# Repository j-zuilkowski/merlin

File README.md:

# Merlin

A personal, non-sandboxed agentic development assistant for macOS. Merlin connects to multiple LLM providers — remote and local — and gives an AI agent full access to your file system, shell, Xcode, GUI automation, and external services to work through development tasks autonomously. It includes a supervisor-worker multi-LLM routing layer and MLX LoRA self-training (MLX-format base models on Apple Silicon) to improve the execute slot on your own accepted sessions over time.

Built with Swift and SwiftUI for macOS 14+. Personal use only — not distributed; build from source via the steps in [`Requirements.md`](Requirements.md).

**Version 2.4.0** (build 26)

Current release gate: v2.4.0 is the full green E2E release gate. A release push requires the full GUI/test/provider/domain battery to pass, a release evidence report, and post-green screenshots. Electronics screenshots must be captured after the full battery is green by opening the generated KiCad files in KiCad, not from static generated images alone.

---

## What it does

## Screenshots

## Documentation

- [User Guide](Merlin/Docs/UserGuide.md) — using Merlin, providers, sessions, workflows, electronics tools, and project discipline.
- [Developer Manual](Merlin/Docs/DeveloperManual.md) — architecture, engine surfaces, tool registry, plugins, and developer workflows.
- [Release Notes v2.4.0](RELEASE-v2.4.0.md) — current release highlights, evidence gates, and screenshots.
- [Release Evidence Report](docs/e2e/2026-06-08-v2.4.0-release/REPORT.md) — gate-by-gate v2.4.0 validation artifacts.

## Capabilities

Merlin runs an agentic loop: you describe a task, the model calls tools (read files, run shell commands, build with Xcode, inspect UI, write code), reads the results, and continues until the task is complete. You review staged changes before they land on disk.

**Multi-project workspace** — a single window holds multiple open projects simultaneously. Each project has its own session list in the sidebar; the content area shows whichever session is active. Workspace state (open projects, active session) persists across relaunches.

**Session history** — every session is saved to disk after each turn, scoped per project. Prior sessions appear in the sidebar with relative timestamps. Sessions can be archived (hidden) or recalled to active status. Session titles are auto-generated from the first user message, matching Claude app and Codex behaviour.

**Multi-LLM Supervisor-Worker** — tasks are classified by complexity and routed to the right LLM slot (execute, reason, orchestrate, vision). A critic layer scores outputs; a planner layer decomposes high-stakes work. Model performance is tracked per-model per-task type and stored for training.

**Electronics / KiCad Domain** — a full electronics workflow built on the bus-backed `plugins/electronics` runtime plugin: raster/PDF schematic ingestion, design-intent approval, Circuit IR generation, concrete component evidence, KiCad project and footprint generation, FreeRouting-backed autoroute, ERC/DRC/SPICE/fab verification gates, vendor-native BOM and order workflows. Evidence-gated completion and high-stakes signoff boundaries block irreversible manufacturing actions without explicit approval.

**Multi-Domain Sessions** — each session carries its own active domain IDs. Switching from a software session to an electronics session is instant; the engine, critic, and task-type routing all follow without touching other open sessions.

**Local Memory Backend** — session memories are stored in an on-device SQLite vector store (`LocalVectorPlugin`, `NLContextualEmbedding`, 512-dim) scoped per project path. xcalibre-server is retained for book-content RAG only.

**Behavioral Reliability** — a circuit breaker halts or warns after consecutive critic failures; a grounding confidence signal (`GroundingReport`) surfaces RAG chunk count, average cosine score, and staleness on every turn so you can see when the model is reasoning over thin or stale retrieval.

**Budget-Aware Execution** (v2.1) — every LLM request is sized to the active provider's context window before it is sent. A pre-flight estimator gates each call; working-set caps bound the system prompt, RAG injection, recent turns, and tool-call bursts independently. Oversized work is decomposed into smaller substeps first, with cross-provider routing to a larger-context model only as a last resort.

**LoRA Self-Training** — on an M4 Mac with 128GB unified memory, Merlin can fine-tune a local **MLX-format** model (via MLX-LM) on your own accepted sessions. Automatic training requires an MLX base; GGUF and HF-safetensors bases cannot be trained by `mlx_lm.lora`. The trained adapter is served by any MLX-native runtime — `mlx_lm.server` (the default), LM Studio, or vLLM-Metal after a one-shot `mlx_lm.fuse` for text-only experiments, though vLLM-Metal is non-working for the current Merlin general+vision pair workflow and should be avoided for the foreseeable future. For GGUF providers (Ollama / Jan.ai / LocalAI / llama.cpp), an additional GGUF-conversion step deploys the fine-tuned model; Mistral.rs cannot serve MoE models on Metal regardless.

**Project Discipline** (v2.2) — Merlin can enforce construction discipline on any project: TDD task pairs, comprehensive user-manual coverage, WHY-comments where warranted, prose readability, and task-file/code sync. Five `/project:*` skills (`init`, `task`, `revise`, `release`, `adopt`) handle creation; a `DisciplineEngine` plus git hooks enforce the rules automatically. `/project:adopt` applies the discipline to an existing codebase.

**Full Green E2E Release Gate** (v2.4) — release readiness is a blocking evidence surface. The current release path requires core tests, GUI bootstrapping, focused visual tests, live-provider coverage, local-provider pair smokes, xcalibre RAG verification, S1/S2 capability convergence, electronics/KiCad verification, service cleanup, and a passing evidence report before tagging or publishing.

See [`FEATURES.md`](FEATURES.md) for a complete capability reference.  
See [`spec.md`](spec.md) for implementation details and design decisions.

---

## Providers

Remote: **Anthropic**, **DeepSeek**, **OpenAI**, **Qwen**, **OpenRouter**

Local provider status (validated live on May 27, 2026):

Preferred local provider: **llama.cpp router mode**. Use it first for local
general+vision work because one router-mode `llama-server` can own the GGUF text
model, the GGUF vision model, and the vision `mmproj` behind one OpenAI-compatible
endpoint. LM Studio and Jan.ai remain reliable alternatives.

| Provider | Status | Notes |
|---|---|---|
| llama.cpp (router mode) | Preferred reliable | First-class provider at `http://localhost:8081/v1`; one router-mode server handled the local general+vision GGUF pair |
| LM Studio | Reliable alternative | General + vision pair passed live calibration |
| Jan.ai | Reliable alternative | General + vision pair passed live calibration |
| LocalAI | Non-working for Merlin full surface | Text, streaming, and vision responded, but tool-call requests returned plain content without OpenAI `tool_calls` |
| Ollama | Non-working for Merlin full surface | Text works, but the tested Qwen3-VL path crashes the runner on real image requests; skip until upstream fixes land |
| vLLM-Metal | Non-working / avoid | Text and auto tool calls can work, but forced tool choice is unreliable and vision is not implemented on Metal; avoid for the foreseeable future |
| Mistral.rs | Non-working for tested model | The tested Qwen3 MoE GGUF model loads, then fails on first inference on Apple Metal |

Upstream blocker tracking for the malfunctioning local providers lives in
[`docs/local-provider-configs/RESULTS.md`](docs/local-provider-configs/RESULTS.md).

`/calibrate` is live-validated in the app against the supported local providers. The GUI flow now completes picker → running → report, surfaces scorer failures materially better than before, and reports degraded critic fallback explicitly when it occurs.

Routing is driven by explicit slot assignments (Execute, Reason, Orchestrate, Vision) in
Settings → Role Slots. The sidebar slot-status panel reflects those assignments directly;
enabled provider inventory alone does not configure routing. API keys are stored in
`~/.merlin/api-keys.json` during Debug/dev-loop builds and in macOS Keychain for
Release builds. The release/pre-push path and CI block tracked local-only key
files such as `api-keys.json`, `.env*`, and `secrets.json`.

---

## Requirements

- macOS 14 (Sonoma) or later
- Xcode 15.4 or later
- [XcodeGen](https://github.com/yonaskolb/XcodeGen) (`brew install xcodegen`)

---

## Build & Run

```bash
# Generate the Xcode project
xcodegen generate

# Build and launch (Debug)
xcodebuild -scheme Merlin -configuration Debug \
    SYMROOT="$(pwd)/build" \
    CODE_SIGNING_ALLOWED=NO 2>&1 | grep -E 'error:|BUILD SUCCEEDED|BUILD FAILED'

open build/Debug/Merlin.app
```

Or open `Merlin.xcodeproj` in Xcode and run from there.

---

## Project layout

```
Merlin/             Main application target (Swift sources)
MerlinTests/        Unit and integration tests
MerlinLiveTests/    Real-provider API tests (run manually)
MerlinE2ETests/     Full agentic loop + UI tests (run manually)
TestHelpers/        Shared test utilities (MockProvider, EngineFactory, …)
TestTargetApp/      Fixture app for GUI automation tests
tasks/             Task-by-task implementation sheets
scripts/            DMG packaging script
```

---

## Configuration

| File | Purpose |
|---|---|
| `~/.merlin/config.toml` | Hooks, memories, reasoning overrides, toolbar actions |
| `~/.merlin/mcp.json` | MCP server definitions |
| `~/.merlin/skills/` | Personal slash-command skills |
| `~/.merlin/agents/` | Custom subagent definitions |
| `~/.merlin/memories/` | Accepted AI-generated memories |
| `~/.merlin/workspace.json` | Open projects and active session (persisted across relaunches) |
| `~/.merlin/layout-workspace.json` | Pane layout (sidebar width, visible panes) |
| `~/Library/Application Support/Merlin/providers.json` | Provider configuration |
| `~/Library/Application Support/Merlin/auth.json` | Auth gate allow/deny patterns |
| `~/Library/Application Support/Merlin/sessions/<project-id>/` | Per-project session history |

---

## Running tests

```bash
# Unit + integration (fast, no network)
xcodebuild -scheme MerlinTests test \
    -destination 'platform=macOS' \
    -derivedDataPath /tmp/merlin-derived 2>&1 \
    | grep -E 'Test.*passed|Test.*failed|BUILD SUCCEEDED|BUILD FAILED'

# Live provider tests (requires API keys)
RUN_LIVE_TESTS=1 xcodebuild -scheme MerlinTests-Live test \
    -destination 'platform=macOS' \
    -derivedDataPath /tmp/merlin-derived
```

---

## Release Readiness

Merlin v2.4.0 is not considered release-push-ready from version metadata alone. The release push requires the full green E2E battery described in [`spec.md`](spec.md): full `MerlinTests`, full `MerlinUITests`, focused visual tests, allowed live-provider skips only for missing keys, local-provider pair smokes with clean shutdown, xcalibre RAG verification, S1/S2 convergence, and electronics/KiCad verification.

After the full battery is green, open the generated KiCad schematic and open the generated KiCad PCB in KiCad, then capture release screenshots of the schematic editor, PCB editor, routed board/layer views, and 3D board view when available. GitHub feature screenshots are captured at the same post-green stage.

Screenshot destinations:

- GitHub Release assets: upload release-marketing screenshots and KiCad screenshots to the `v2.4.0` GitHub Release as release assets.
- README-linked screenshots: commit durable public images under `docs/assets/screenshots/v2.4.0/`.
- Evidence-only screenshots: retain validation-only images under `docs/e2e/<date>-v2.4.0-release/screenshots/` with the E2E report.

---

## Packaging

```bash
bash scripts/package-dmg.sh <version>
# → dist/Merlin-<version>.dmg
```

Or build a release DMG directly:

```bash
xcodebuild -scheme Merlin -configuration Release \
    -derivedDataPath /tmp/merlin-release \
    -destination 'platform=macOS' build

hdiutil create -volname "Merlin <version>" \
    -srcfolder /tmp/merlin-release/Build/Products/Release/Merlin.app \
    -ov -format UDZO dist/Merlin-$(date +%Y-%m-%d)-v<version>.dmg
```

Requires [`create-dmg`](https://github.com/create-dmg/create-dmg) (`brew install create-dmg`) or falls back to `hdiutil`.

---

## Further reading

- [`FEATURES.md`](FEATURES.md) — complete feature reference
- [`spec.md`](spec.md) — system design and implementation decisions
- [`llm.md`](llm.md) — LLM provider and context design details
- [`skill-standard.md`](skill-standard.md) — skill and plugin authoring guide
- [User Guide](Merlin/Docs/UserGuide.md) — in-app user guide (Help menu)
- [Developer Manual](Merlin/Docs/DeveloperManual.md) — in-app developer reference (Help menu)
- [Release Notes v2.4.0](RELEASE-v2.4.0.md) — current release notes

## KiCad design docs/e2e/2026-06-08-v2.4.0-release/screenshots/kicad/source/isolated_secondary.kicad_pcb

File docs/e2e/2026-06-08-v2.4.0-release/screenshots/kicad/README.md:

# KiCad Screenshot Evidence - Task 512

This bundle supersedes the Task 511 KiCad screenshots. Task 512 regenerated the
source artifacts from the final green AmpDemo PCB slice, reopened those copied
files in KiCad 10.0.3, and captured fresh editor screenshots after user review
found the prior evidence unusable.

## Source

- `source/isolated_secondary.kicad_pro`
- `source/isolated_secondary.kicad_sch`
- `source/isolated_secondary.kicad_pcb`
- `source/8FDFC0B1-C9C8-4CED-9E02-9374462932BA-component_matrix.json`
- `source/94B2FA49-5634-45BD-AB71-95C35C9E8A75-footprint_assignment.json`
- `source/drc.json`
- `source/drc-rerun.json`

## Screenshots And Exports

- `schematic-editor-screenshot.png` - copied schematic opened in KiCad
  Schematic Editor; visible connectors include `JSEC`, `JIN`, and `JSPK`.
- `pcb-editor-screenshot.png` - copied board opened in KiCad PCB Editor with
  visible routed copper; the KiCad status bar shows 62 pads, 36 vias, 72 track
  segments, 18 nets, and 0 unrouted items.
- `board-3d-viewer-screenshot.png` - copied board opened in KiCad GUI 3D
  Viewer.
- `schematic.pdf` - KiCad CLI schematic PDF export.
- `schematic-svg/isolated_secondary.svg` and
  `schematic-svg/isolated_secondary.png` - KiCad CLI schematic export and PNG
  preview.
- `layers/front-copper.svg` and `layers/front-copper.png` - front copper/layer
  export.
- `layers/back-copper.svg` and `layers/back-copper.png` - back copper/layer
  export.
- `layers/routed-composite.svg` and `layers/routed-composite.png` - combined
  routed/layer export.
- `board-3d-render.png` - deterministic KiCad CLI 3D render.

## Verification

`source/drc.json` is the runtime DRC report from the final green generated
board. It records:

- 0 DRC violations
- 0 unconnected items
- 0 schematic parity issues
- KiCad 10.0.3

`source/drc-rerun.json` is the copied-project KiCad CLI rerun. It records 0 DRC
violations and 0 unconnected items, with 59 schematic parity warnings. That
copied-bundle parity limitation is preserved as evidence and this screenshot
bundle is not a `FAB_READY` claim.

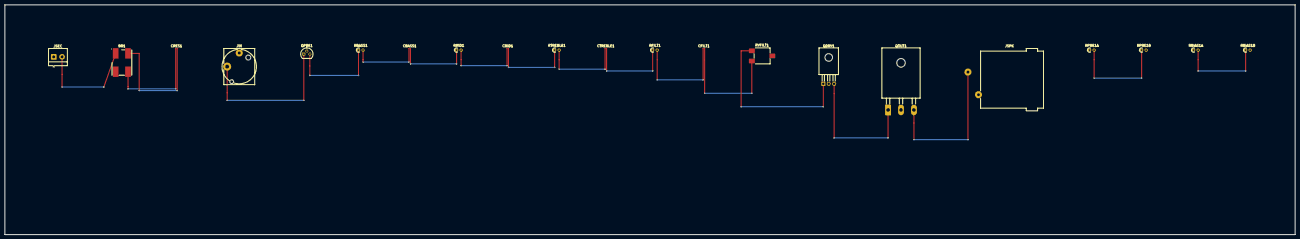
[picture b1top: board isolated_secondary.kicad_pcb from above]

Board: 2 copper layers, 543.6 x 96.8 mm, 21 parts (0 on the bottom side), 18 nets.

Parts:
BR1: BR1-MPN; Diode_Bridge_Bourns_CD-DF4xxS
CBASS1: 100nF; C_0201_0603Metric
CFILT1: 47nF; C_0201_0603Metric
CMID1: 22nF; C_0201_0603Metric
CRES1: 10000uF; C_0201_0603Metric
CTREBLE1: 470pF; C_0201_0603Metric
JIN: JIN-MPN; Jack_6.35mm_Neutrik_NJ2FD-V_Vertical
JSEC: JSEC-MPN; TerminalBlock_4Ucon_1x02_P3.50mm_Horizontal
JSPK: JSPK-MPN; Jack_speakON_Neutrik_NL2MDXX-H-3_Horizontal
QDRV1: QDRV1-MPN; TO-126-3_Horizontal_TabDown
QOUT1: QOUT1-MPN; TO-247-3_Horizontal_TabDown
QPRE1: QPRE1-MPN; TO-92
RBASS1: 1MOhm; R_Axial_DIN0204_L3.6mm_D1.6mm_P1.90mm_Vertical
RBIAS1A: 10kOhm; R_Axial_DIN0204_L3.6mm_D1.6mm_P1.90mm_Vertical
RBIAS1B: 1kOhm; R_Axial_DIN0204_L3.6mm_D1.6mm_P1.90mm_Vertical
RFILT1: 10kOhm; R_Axial_DIN0204_L3.6mm_D1.6mm_P1.90mm_Vertical
RMID1: 25kOhm; R_Axial_DIN0204_L3.6mm_D1.6mm_P1.90mm_Vertical
RPRE1A: 1MOhm; R_Axial_DIN0204_L3.6mm_D1.6mm_P1.90mm_Vertical
RPRE1B: 100kOhm; R_Axial_DIN0204_L3.6mm_D1.6mm_P1.90mm_Vertical
RTREBLE1: 250kOhm; R_Axial_DIN0204_L3.6mm_D1.6mm_P1.90mm_Vertical
RVFILT1: 100kOhm; Potentiometer_ACP_CA6-VSMD_Vertical

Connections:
AC_SEC1: BR1.1, JSEC.2
DRV_OUT: QDRV1.3, QOUT1.1
FILTER1_INTERNAL_CFILT1_RVFILT1: CFILT1.2, RVFILT1.1
FILTER1_INTERNAL_RFILT1_CFILT1: CFILT1.1, RFILT1.2
FILTER_OUT: QDRV1.1, RVFILT1.3
GND: BR1.4, CRES1.2
GUITAR_IN: JIN.S, QPRE1.1
PRE_OUT: QPRE1.3, RBASS1.1
RBIAS1_INTERNAL_RBIAS1A_RBIAS1B: RBIAS1A.2, RBIAS1B.1
RPRE1_INTERNAL_RPRE1A_RPRE1B: RPRE1A.2, RPRE1B.1
SPK_OUT: JSPK.1+, QOUT1.3
TONE1_INTERNAL_CBASS1_RMID1: CBASS1.2, RMID1.1
TONE1_INTERNAL_CMID1_RTREBLE1: CMID1.2, RTREBLE1.1
TONE1_INTERNAL_RBASS1_CBASS1: CBASS1.1, RBASS1.2
TONE1_INTERNAL_RMID1_CMID1: CMID1.1, RMID1.2
TONE1_INTERNAL_RTREBLE1_CTREBLE1: CTREBLE1.1, RTREBLE1.2
TONE_OUT: CTREBLE1.2, RFILT1.1
VRAW: BR1.3, CRES1.1

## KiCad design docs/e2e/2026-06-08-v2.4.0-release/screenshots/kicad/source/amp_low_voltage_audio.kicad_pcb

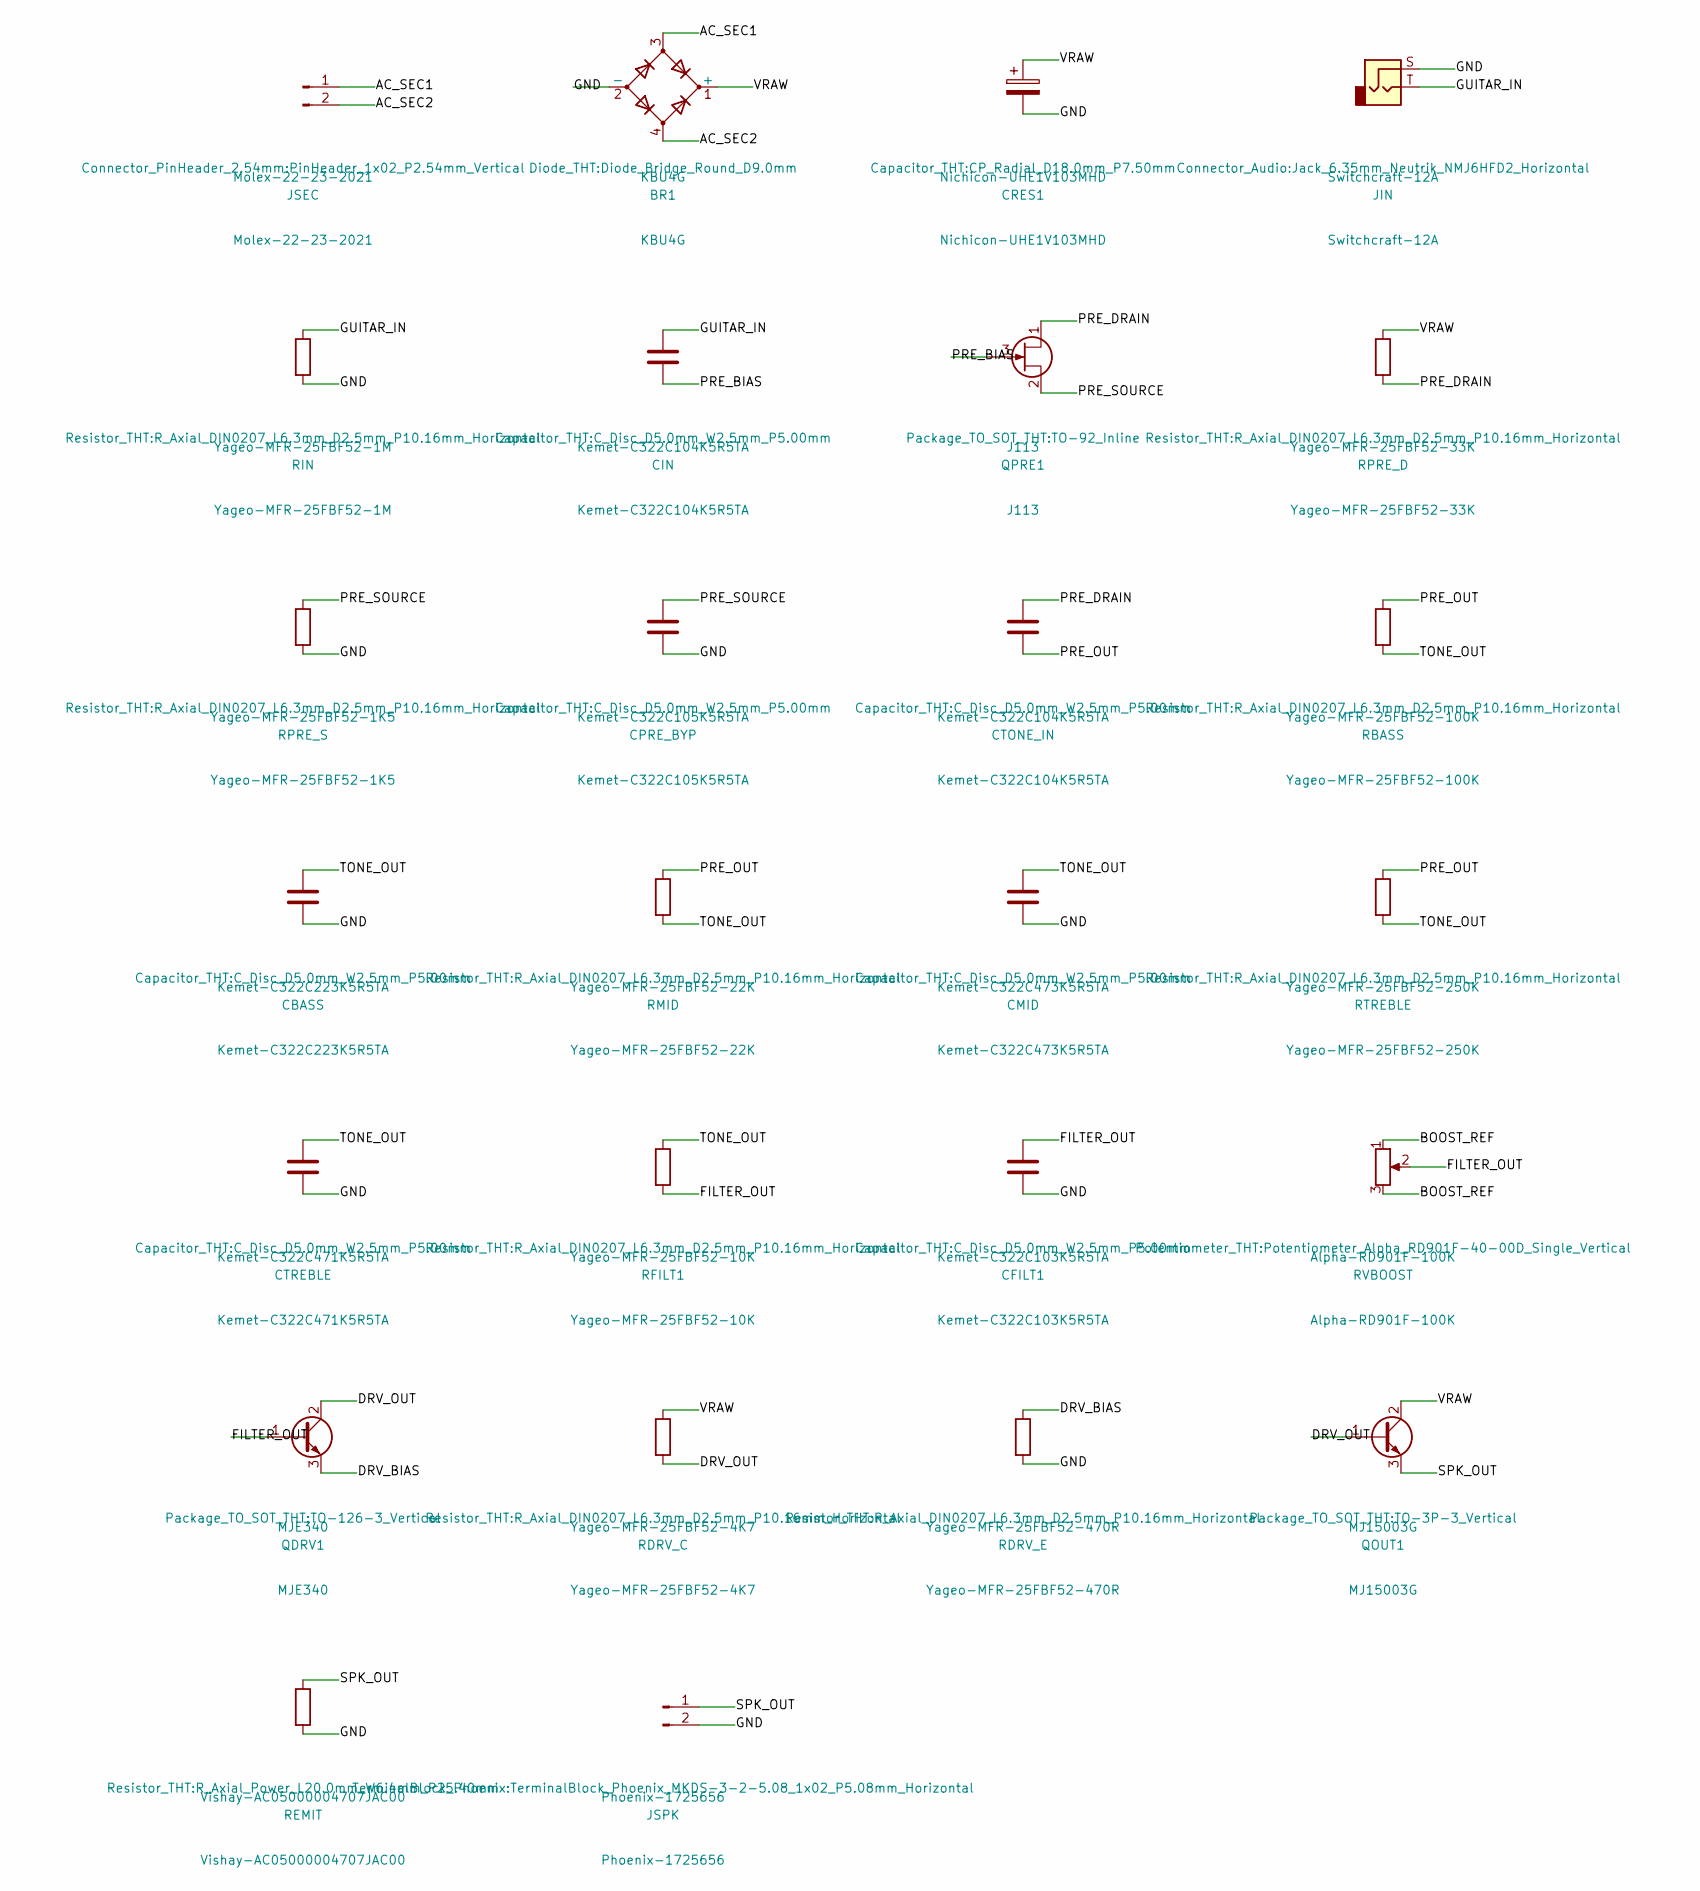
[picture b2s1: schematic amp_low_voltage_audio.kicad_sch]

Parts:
BR1: KBU4G; Diode_Bridge_Round_D9.0mm; ManufacturerPartNumber KBU4G
CBASS: Kemet-C322C223K5R5TA; C_Disc_D5.0mm_W2.5mm_P5.00mm; ManufacturerPartNumber Kemet-C322C223K5R5TA
CFILT1: Kemet-C322C103K5R5TA; C_Disc_D5.0mm_W2.5mm_P5.00mm; ManufacturerPartNumber Kemet-C322C103K5R5TA
CIN: Kemet-C322C104K5R5TA; C_Disc_D5.0mm_W2.5mm_P5.00mm; ManufacturerPartNumber Kemet-C322C104K5R5TA
CMID: Kemet-C322C473K5R5TA; C_Disc_D5.0mm_W2.5mm_P5.00mm; ManufacturerPartNumber Kemet-C322C473K5R5TA
CPRE_BYP: Kemet-C322C105K5R5TA; C_Disc_D5.0mm_W2.5mm_P5.00mm; ManufacturerPartNumber Kemet-C322C105K5R5TA
CRES1: Nichicon-UHE1V103MHD; CP_Radial_D18.0mm_P7.50mm; ManufacturerPartNumber Nichicon-UHE1V103MHD
CTONE_IN: Kemet-C322C104K5R5TA; C_Disc_D5.0mm_W2.5mm_P5.00mm; ManufacturerPartNumber Kemet-C322C104K5R5TA
CTREBLE: Kemet-C322C471K5R5TA; C_Disc_D5.0mm_W2.5mm_P5.00mm; ManufacturerPartNumber Kemet-C322C471K5R5TA
JIN: Switchcraft-12A; Jack_6.35mm_Neutrik_NMJ6HFD2_Horizontal; ManufacturerPartNumber Switchcraft-12A
JSEC: Molex-22-23-2021; PinHeader_1x02_P2.54mm_Vertical; ManufacturerPartNumber Molex-22-23-2021
JSPK: Phoenix-1725656; TerminalBlock_Phoenix_MKDS-3-2-5.08_1x02_P5.08mm_Horizontal; ManufacturerPartNumber Phoenix-1725656
QDRV1: MJE340; TO-126-3_Vertical; ManufacturerPartNumber MJE340
QOUT1: MJ15003G; TO-3P-3_Vertical; ManufacturerPartNumber MJ15003G
QPRE1: J113; TO-92_Inline; ManufacturerPartNumber J113
RBASS: Yageo-MFR-25FBF52-100K; R_Axial_DIN0207_L6.3mm_D2.5mm_P10.16mm_Horizontal; ManufacturerPartNumber Yageo-MFR-25FBF52-100K
RDRV_C: Yageo-MFR-25FBF52-4K7; R_Axial_DIN0207_L6.3mm_D2.5mm_P10.16mm_Horizontal; ManufacturerPartNumber Yageo-MFR-25FBF52-4K7
RDRV_E: Yageo-MFR-25FBF52-470R; R_Axial_DIN0207_L6.3mm_D2.5mm_P10.16mm_Horizontal; ManufacturerPartNumber Yageo-MFR-25FBF52-470R
REMIT: Vishay-AC05000004707JAC00; R_Axial_Power_L20.0mm_W6.4mm_P25.40mm; ManufacturerPartNumber Vishay-AC05000004707JAC00
RFILT1: Yageo-MFR-25FBF52-10K; R_Axial_DIN0207_L6.3mm_D2.5mm_P10.16mm_Horizontal; ManufacturerPartNumber Yageo-MFR-25FBF52-10K
RIN: Yageo-MFR-25FBF52-1M; R_Axial_DIN0207_L6.3mm_D2.5mm_P10.16mm_Horizontal; ManufacturerPartNumber Yageo-MFR-25FBF52-1M
RMID: Yageo-MFR-25FBF52-22K; R_Axial_DIN0207_L6.3mm_D2.5mm_P10.16mm_Horizontal; ManufacturerPartNumber Yageo-MFR-25FBF52-22K
RPRE_D: Yageo-MFR-25FBF52-33K; R_Axial_DIN0207_L6.3mm_D2.5mm_P10.16mm_Horizontal; ManufacturerPartNumber Yageo-MFR-25FBF52-33K
RPRE_S: Yageo-MFR-25FBF52-1K5; R_Axial_DIN0207_L6.3mm_D2.5mm_P10.16mm_Horizontal; ManufacturerPartNumber Yageo-MFR-25FBF52-1K5
RTREBLE: Yageo-MFR-25FBF52-250K; R_Axial_DIN0207_L6.3mm_D2.5mm_P10.16mm_Horizontal; ManufacturerPartNumber Yageo-MFR-25FBF52-250K
RVBOOST: Alpha-RD901F-100K; Potentiometer_Alpha_RD901F-40-00D_Single_Vertical; ManufacturerPartNumber Alpha-RD901F-100K

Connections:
AC_SEC1: BR1.3, JSEC.1
AC_SEC2: BR1.4, JSEC.2
BOOST_REF: RVBOOST.1, RVBOOST.3
DRV_BIAS: QDRV1.3 (E), RDRV_E.1
DRV_OUT: QDRV1.2 (C), QOUT1.1 (B), RDRV_C.2
FILTER_OUT: CFILT1.1, QDRV1.1 (B), RFILT1.2, RVBOOST.2
GND: BR1.2 (-), CBASS.2, CFILT1.2, CMID.2, CPRE_BYP.2, CRES1.2, CTREBLE.2, JIN.S, JSPK.2, RDRV_E.2, REMIT.2, RIN.2, RPRE_S.2
GUITAR_IN: CIN.1, JIN.T, RIN.1
PRE_BIAS: CIN.2, QPRE1.3 (G)
PRE_DRAIN: CTONE_IN.1, QPRE1.1 (D), RPRE_D.2
PRE_OUT: CTONE_IN.2, RBASS.1, RMID.1, RTREBLE.1
PRE_SOURCE: CPRE_BYP.1, QPRE1.2 (S), RPRE_S.1
SPK_OUT: JSPK.1, QOUT1.3 (E), REMIT.1
TONE_OUT: CBASS.1, CMID.1, CTREBLE.1, RBASS.2, RFILT1.1, RMID.2, RTREBLE.2
VRAW: BR1.1 (+), CRES1.1, QOUT1.2 (C), RDRV_C.1, RPRE_D.1

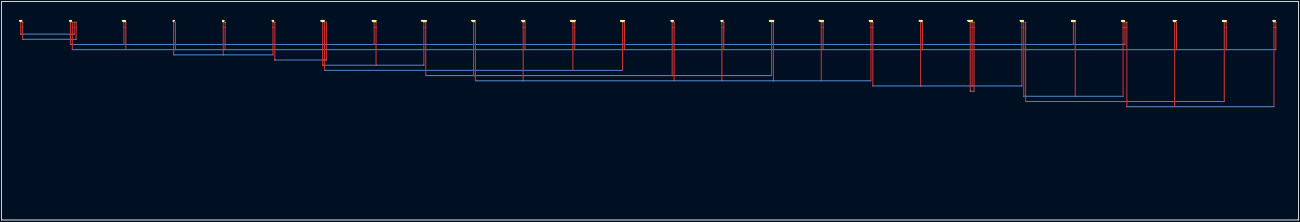
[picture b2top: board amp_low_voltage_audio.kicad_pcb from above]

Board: 2 copper layers, 1751.3 x 295.0 mm, 26 parts (0 on the bottom side), 15 nets.

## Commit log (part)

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2026-05-16 Phase 294a — RAG sources HTML tests (failing)
2026-05-16 Phase 294b — RAG sources HTML
2026-05-16 Phase 295a — Subagent block HTML tests (failing)
2026-05-16 Phase 296a — Subagent sidebar tests (failing)
2026-05-16 Phase 296b — Subagent sidebar
2026-05-16 Phase 297b — merlin-discipline CLI
2026-05-16 Phase 298a — Discipline event stream tests (failing)
2026-05-16 Phase 298b — Discipline event stream
2026-05-16 Phase 299b — Git hook wiring
2026-05-16 Phase 300a — Discipline generator tools tests (failing)
2026-05-16 Phase 301 — Remove unused versionBumpCandidate finding category
2026-05-16 Phase 302a — Info.plist permission strings tests (failing)
2026-05-16 Phase 302c — Revive the MerlinTests-Live scheme (post-145b rot)
2026-05-16 Phase 303a — Eval harness tests (failing)
2026-05-16 Phase 303b — Eval harness
2026-05-16 Phase 304b — Discipline chip shows true finding count
2026-05-16 Phase 305 — Wire the dead View-menu commands
2026-05-16 Phase 306b — Accessibility-identifier pass across the UI surface
2026-05-16 Relocate SURFACE-INVENTORY.md into phases/; track Liveness Discipline batch
2026-05-16 Phase 307b — TargetGateScanner: flag targets the build gate never compiles
2026-05-16 Phase 308a — StubMarkerScanner tests (failing)
2026-05-16 Phase 308b — StubMarkerScanner: surface unfinished code as discipline findings
2026-05-16 Phase 309b — ReachabilityScanner: flag unwired views and uninjected env objects
2026-05-16 Phase 310a — DocReferenceGraph fenced-block tests (failing)
2026-05-16 Phase 311a — LivenessGate tests (failing)
2026-05-16 Phase 311b — LivenessGate: pre-commit hook blocks ungated targets
2026-05-16 Phase 313a — Discipline gate auto-install tests (failing)
2026-05-16 Phase 313b — Auto-arm the discipline pre-commit gate at app launch
2026-05-16 Phase 314a — TargetGateScanner dependency-following tests (failing)
2026-05-16 Phase 315a — merlin-discipline scan command tests (failing)
2026-05-16 Phase 315b — merlin-discipline scan: print all discipline findings
2026-05-16 Phase 316b — DocReferenceGraph skips phases/ and knows test symbols
2026-05-16 Phase 317a — ReachabilityScanner injection-detection tests (failing)
2026-05-16 Phase 318a — StubMarkerScanner tuning tests (failing)
2026-05-16 Phase 318b — StubMarkerScanner skips .cancel buttons and multi-line strings
2026-05-17 Phase 319a — DocReferenceGraph precision tests (failing)
2026-05-17 Phase 320a — WorkerDiffViewActionTests (failing)
2026-05-17 Phase 320b — Wire WorkerDiffView reject-all / accept-and-merge
2026-05-17 Phase 321b — DocReferenceGraph extractEnumCaseNames strips // comments
2026-05-17 Phase 322 — Remove dead TelemetryEmitter setters
2026-05-17 Phase 323a — PhaseScanner doc-coverage & drift-severity tests (failing)
2026-05-17 Phase 324a — PhaseScanner symbol-matching tests (failing)
2026-05-17 Phase 324b — PhaseScanner symbol-matching accuracy
2026-05-17 Phase 325b — AccessibilityID gap-fill: the 12 controls phase 306 missed
2026-05-17 Phase 326 — Eval capability harness (S1–S6), self-launching services
2026-05-17 Phase 328 — Eval surface harness (S7–S11)
2026-05-17 Phase 329 — Eval render harness (S10 chat rendering)
2026-05-17 Phase 330 — Eval operator harness (S12–S17)
2026-05-17 Phase 331b — DisciplineExclusions blacklist
2026-05-17 Phase 332 — Relocate merlin-eval into the merlin repo
2026-05-17 Sync architecture.md discipline enums with implemented code
2026-05-17 Fix MerlinTests-Live scheme: RUN_LIVE_TESTS env var was a malformed nested mapping
2026-05-17 Fix EvalLMStudio: resolve LM Studio model from slot assignments, not the empty provider model field
2026-05-17 Fix LoRATrainer: invoke python3, not bare python (not present on macOS)
2026-05-17 Fix HARNESS-4: run cargo/python via zsh so the user PATH is sourced (env: cargo not found)
2026-05-20 Phase 333b — RedundantDocstringScanner
2026-05-20 Phase 336a — LoRAServingTargetSettingsTests (failing)
2026-05-23 Repair runtime workflows and reconcile docs
2026-05-24 Classify local model exposure
2026-05-24 Harden scheduler firing
2026-05-24 Restore electronics activation
2026-05-24 Resolve virtual active providers
2026-05-24 Fix subagent UI completion and diff selection
2026-05-24 Fix domain activation and first-launch persistence
2026-05-24 Phase 338a — llama.cpp router provider tests (failing)
2026-05-24 Phase 338b — llama.cpp first-class router provider
2026-05-24 Phase 339b — move routing status to sidebar slot panel
2026-05-24 Phase 340a — documentation sweep tests (failing)
2026-05-24 Phase 340b — reconcile documentation after llama.cpp and slot status panel
2026-05-24 Document llama.cpp router and slot status architecture
2026-05-25 Close llama.cpp router and slot status gaps
2026-05-25 Phase 341b — CAG foundation and stable request policy
2026-05-25 Phase 342a — CAG provider and metrics tests (failing)
2026-05-25 Phase 342b — CAG Anthropic cache control and metrics
2026-05-25 Phase 343b — document CAG and refresh architecture status
2026-05-25 Wire CAG files into Xcode project
2026-05-25 Fix CI unit test diagnostics
2026-05-25 Stabilize prose readability missing config test
2026-05-25 Make prose readability test deterministic
2026-05-25 Task 344a — SDD artifact cutover tests
2026-05-25 Task 344b — SDD artifact cutover
2026-05-25 Task 345b — project task skill
2026-05-25 Task 346a — SDD documentation sweep tests
2026-05-26 Task 347 — SDD traceability gate
2026-05-26 Spec workspace message bus architecture
2026-05-26 Task 348a — workspace message bus foundation tests (failing)
2026-05-26 Task 348b — workspace message bus foundation
2026-05-26 Task 349a — tool router bus cutover tests (failing)
2026-05-26 Task 350a — origin MCP domain bus tests (failing)
2026-05-26 Task 350b — share workspace bus across sessions and transports
2026-05-26 Task 351b — workspace settings events artifacts and docs
2026-05-26 Task 352a — runtime plugin loader tests (failing)
2026-05-26 Task 353a — electronics plugin migration tests (failing)
2026-05-26 Task 353b — migrate electronics plugin to workspace bus
2026-05-26 Fix CI test stabilization after bus cutover
2026-05-26 Task 354b — archive legacy MCP scaffold
2026-05-26 Task 355-359 — spec electronics completion pass
2026-05-26 Task 355b — electronics completion contract
2026-05-26 Task 356a — local FreeRouting tests
2026-05-26 Task 357a — electronics artifact gate tests
2026-05-26 Task 357b — electronics artifacts and gates
2026-05-26 Task 358a — electronics job panel tests
2026-05-26 Task 359a — electronics completion docs tests
2026-05-26 Task 359b — electronics completion docs
2026-05-26 Tasks 360a-374a — plugin electronics gap tests
2026-05-26 Tasks 360b-374b — close plugin electronics gaps
2026-05-26 Task 375a — electronics green-board tests
2026-05-26 Task 376a — full green runtime electronics tests
2026-05-26 Task 376b — full green runtime electronics
2026-05-26 Add native web search vision
2026-05-27 Stabilize Merlin E2E gates
    - Add reliable MerlinUITests scheme/bootstrap and visual coverage
    - Fix OCR/KiCad runtime evidence and local provider smoke documentation
    - Archive retired full-battery harness and record current eval status
    Verified: MerlinTests 2138 tests / 49 skipped / 0 failures; MerlinUITests 12 tests / 0 failures.
2026-05-28 Stabilize E2E and bump version to 2.3.0
2026-05-28 Fix CI electronics workflow tests
2026-05-28 Stabilize discipline missing-config test
2026-05-29 Add live electronics job leaderboard
2026-05-29 Harden AmpDemo electronics workflow gates
2026-05-29 Block AmpDemo placeholder electronics completion
2026-05-29 Build generic electronics plugin workflow
2026-05-29 Wire electronics harness evidence flow
2026-05-29 Accept electronics evidence artifact paths
2026-05-29 Preserve electronics tool failure evidence
2026-05-30 Add electronics evidence-gated catalog workflow
2026-05-30 Route electronics compile gates by evidence stage
2026-05-30 Bridge CircuitIR selection and footprints
2026-05-30 Wire runtime electronics provider evidence
2026-05-30 Add electronics handoff orchestration gates
2026-05-30 Add electronics validation repair gates
2026-05-30 Add electronics runtime repair actions
2026-05-30 Make electronics KiCad outputs validation-clean
2026-05-30 Add electronics DesignIntent approval continuation
2026-05-31 Tone down near-ceiling continuation warning
2026-05-31 Block unresolved component selection
2026-06-01 Gate schematic verification on KiCad evidence
2026-06-01 Preserve validation diagnostics in electronics workflow
2026-06-01 Stop electronics workflow after blocked validation
2026-06-01 Surface electronics plugin settings dynamically
2026-06-01 Lock electronics workflows to domain tools
2026-06-01 Require design-producing electronics boundary
2026-06-01 Stop electronics workflow on blocked tool results
2026-06-01 Require vendor artifact evidence for BOM steps
2026-06-02 Fix focused electronics continuation handoff drift
2026-06-02 Add electronics vendor evidence providers
2026-06-03 Add evidence-backed footprint assignment
2026-06-03 Gate schematic compilation on evidence
2026-06-03 Embed KiCad footprint bodies in PCB materializer
2026-06-03 Gate PCB completion on clean KiCad DRC evidence
2026-06-05 Harden electronics workflow execution gates
2026-06-05 Keep electronics plans evidence gated
2026-06-05 Recover electronics handoffs from artifact files
2026-06-05 Harden electronics BOM and footprint handoffs
2026-06-05 Block unresolved component matrices
2026-06-06 Gate schematic compile on catalog evidence
2026-06-06 Fix evidence-backed PCB routing DRC gate
2026-06-06 Cache electronics datasheet PDFs locally
2026-06-06 Prioritize critical parts in live catalog queries
2026-06-06 Task 458b — AmpDemo PCB layout evidence gates
2026-06-06 Task 460 — harden live catalog cache gating
2026-06-06 Tasks 439-444 — mark repair actions complete
2026-06-06 Task 462 — record AmpDemo PCB DRC slice
2026-06-06 Task 463 — gate SPICE measurements by envelope
2026-06-06 Task 464 — require explicit SPICE scenarios
2026-06-06 Task 466: wire full workflow SPICE gates
2026-06-06 Task 467: gate schematic realism
2026-06-06 Task 468: gate generic board decomposition
2026-06-07 Task 469: scope topology materialization
2026-06-07 Task 471: gate DRC layout rerun evidence
2026-06-07 Task 472: mutate PCB DRC repair plans
2026-06-07 Task 473: gate vendor BOM evidence
2026-06-07 Task 475: synchronize electronics GUI job state
2026-06-07 Task 476: mutate DRC routing repairs natively
2026-06-07 Task 478: add component selection revision workflow
2026-06-07 Task 479: surface component revision questions
2026-06-07 Task 480: recover component revision answers
2026-06-07 Task 482: define electronics finish checklist
2026-06-07 Task 483: add GUI resolver answer entry
2026-06-08 Task 485: record fresh GUI workflow context blocker
2026-06-08 Task 486 - cap electronics artifact context reads
2026-06-08 Task 488 - finalize electronics completion contract status
2026-06-08 Task 489: sync developer manual with source
2026-06-08 Bump version to 2.4.0
2026-06-08 Update README for v2.4.0 release gate
2026-06-08 Document release screenshot destinations
2026-06-08 Task 491: make KiCad gates evidence-scoped
2026-06-08 Task 492: add resumable release run ledger
2026-06-08 Task 494: pass release UI gates
2026-06-08 Task 495: pass release live DeepSeek gate
2026-06-08 Task 496: pass release local provider gate
2026-06-08 Task 498: pass release xcalibre RAG gate
2026-06-11 Task 499: close failed capability gate attempts
2026-06-11 Task 501 - repair release capability model preflight
2026-06-11 Task 502 - repair S1 verification continuation loop
2026-06-11 Task 504 - pass release electronics KiCad gate
2026-06-11 Task 505 - capture release KiCad screenshots
2026-06-11 Task 506 - capture release README screenshots
2026-06-11 Task 508 - pass final release safety check
2026-06-11 Task 509 - record invalid KiCad release evidence
2026-06-11 Task 511 - rerun release KiCad screenshots
2026-06-11 Task 512: repair KiCad usability evidence
2026-06-12 Task 514: create v2.4.0 tag
2026-06-12 Task 515: sweep documentation references
2026-06-12 Task 516: place release screenshots and publish
2026-06-12 Task 517: embed bundled KiCad symbols for CI
2026-06-12 Task 518: publish release documentation
2026-06-12 Add Web Search MCP plugin
